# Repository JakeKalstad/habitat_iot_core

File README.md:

# Habitat IoT

**Rust firmware and hardware designs for connected sensors and actuators, built around the ESP32.**

Habitat began in 2023 as the device side of a larger IoT platform. It brings together embedded firmware, browser-based Wi-Fi setup, local device management, sensor telemetry, and hardware designs in one project.

The original implementation predates our use of LLM-assisted development. We are releasing it so others can study the design, reuse the device interfaces, and build on the work.

**This release covers the device side. The platform it originally integrated with remains proprietary and is not included.** You can build an independent integration using the HTTP endpoints, MQTT messages, and shared Rust types described below. Access to the original platform is not supplied with this repository.

## What is here

- ESP32 firmware written in Rust, using ESP-IDF through `esp-idf-svc` and `esp-idf-hal`.
- Browser-based Wi-Fi provisioning and a local administration page.
- Persistent Wi-Fi, device, and MQTT settings in ESP32 non-volatile storage (NVS).
- Local HTTP endpoints for health information, sensor readings, and configuration.
- Optional MQTT publishing and mDNS service discovery.
- Compile-time modules for environmental sensors, digital inputs, a display, and actuators.
- Shared message types, a simulated device publisher, KiCad designs, and enclosure files.

The firmware uses ESP-IDF and its native components; this is a Rust application on ESP-IDF rather than a `no_std` implementation of the entire device stack.

## Scope and status

This is a historical engineering project being prepared for public use. The supplied snapshot includes later dependency updates and development tooling; it is not a frozen copy of the 2023 toolchain.

The code should be treated as a development starting point. A clean build and physical-device validation are still required for each board and feature combination. Some optional paths are incomplete, hardware configuration needs review, and infrastructure files retain assumptions from the original private environment.

The proprietary hub/backend, platform application, and production services are outside this release. References to them in configuration and deployment files describe the original environment, not services that this repository provides.

## Repository layout

| Path | Purpose |
| --- | --- |
| `iot-core/` | ESP32 firmware, embedded web pages, sensor acquisition, networking, and actuator code. |
| `iot-common/` | Shared serializable types, feature names, and discovery constants. |
| `fake_device/` | Host-side MQTT publisher producing simulated device readings. |
| `schematics/` | KiCad circuit and PCB designs, including environmental sensing boards. |
| `enclosure/` | Enclosure and 3D-print assets, plus reference board files. |
| `pcd8544/` | Local PCD8544 display driver dependency. |
| `kicad-rs/` | KiCad integration library and examples. |
| `devops/` | Historical build, verification, and deployment tooling. Not a standalone platform distribution. |

These are separate Cargo projects, not a single root Cargo workspace. Run commands from the relevant crate directory.

## How a device operates

1. Load the device definition embedded from `iot-core/src/config.json` and any saved user settings from NVS.
2. Scan for Wi-Fi networks. If no SSID is stored, start a setup access point and serve the provisioning page.
3. Save the submitted Wi-Fi settings and restart into client mode.
4. Join the configured network and expose the local administration and data endpoints.
5. Synchronize time with SNTP, perform the hub MQTT discovery query, and enter the acquisition loop.
6. Collect readings from the compiled-in modules and, when enabled, publish them to the configured MQTT broker.

The loop includes a one-second delay, but sensor operations add latency. This is not a guaranteed one-second sampling interval. The current startup path also waits for time synchronization before acquisition begins.

## Build and flash

### Requirements

- An ESP32 board compatible with the configured `xtensa-esp32-espidf` target, a USB data connection, and serial-port access.
- Rust with the Espressif `esp` toolchain, normally installed through `espup`, including `rust-src`.
- `ldproxy` and `espflash` available on your path.
- The native build prerequisites required by ESP-IDF and `embuild` on your host.
- A Wi-Fi network and, if using MQTT, a reachable broker.

The checked-in build configuration selects:

| Setting | Value |
| --- | --- |
| Rust toolchain | `esp` |
| Target | `xtensa-esp32-espidf` |
| MCU | `esp32` |
| ESP-IDF | `v5.2` |
| Runner | `espflash flash --monitor` |

Load the environment exported by your Espressif toolchain installation before building. Preserve the sibling `iot-common/` and `pcd8544/` directories: the firmware manifest references both through local paths.

### Start with a sensorless device

Review `iot-core/src/config.json`, assign a unique device `id`, and check the build notes below. Then, from the repository root:

```sh
cd iot-core
cargo build --release --features bare
cargo run --release --features bare
```

`cargo run` invokes the configured flash-and-monitor runner. These are the intended commands for this configuration, not a claim that this snapshot has been verified against a current toolchain.

Once the bare device works, enable the module you have wired, for example:

```sh
cargo run --release --features bare,temp_humidity
```

Features select firmware code at compile time. Adding an entry to `config.json` does not enable its driver.

## Device configuration

`iot-core/src/config.json` is embedded at build time. It describes device identity, model/version metadata, and feature wiring. Changes require a rebuild and reflash.

A minimal sensorless definition is:

```json
{
  "id": "bench-01",
  "version": "alpha",
  "model": "esp32-wroom",
  "features": {
    "bare": {
      "name": "bare",
      "description": "Sensorless development device",
      "connection_type": "none",
      "hardware_compatible": [],
      "pins": {}
    }
  }
}
```

Use a different ID for each physical device. The supplied `proto-1` value is a development identifier, not an automatically generated serial number.

Wi-Fi credentials, device name/location, and MQTT settings are configured through the device's web interface and saved separately in NVS. They are not part of this build-time JSON.

### Firmware features

| Cargo feature | Implementation / intended role |
| --- | --- |
| `bare` | Sensorless status payload: `{"message":"Here and happy"}`. |
| `temp_humidity` | DHT11 acquisition path; temperature and humidity fields. |
| `temp_pressure` | BMP280 acquisition path; temperature and pressure fields. |
| `motion_sensor` | Digital input reported as a boolean state. |
| `water_sensor` | ADC reading reported as a numeric value. |
| `reed_switch` | Digital input reported as a boolean state. |
| `air_quality` | SGP30 CO₂-equivalent and TVOC readings. |
| `display` | PCD8544 display output using the local driver. |
| `servo` | PWM servo implementation with local HTTP control. |
| `motor` | Experimental L298N motor path; HTTP route registration is commented out. |
| `reset_volatile` | Removes saved Wi-Fi SSID/key at startup; does not clear all device settings. |

Do not enable every feature together by default. Pins, buses, peripheral ownership, and driver compatibility must be checked for the selected combination. The `host` feature is declared but does not establish a host build of the ESP32 firmware.

### Wiring limitations in this snapshot

Treat the configuration as a starting point, not a verified wiring guide:

- The motion configuration names GPIO20, which is absent from the firmware's GPIO map. Its HC-SR04 label also does not match the implemented single-pin boolean acquisition path.
- Several sensor pins in the supplied JSON are absent from the current dynamic GPIO map. Reconcile the map and configuration before enabling those modules.
- The temperature/humidity path calls the DHT11 driver even though the configuration also lists DHT12. Validate the conversion/scaling against actual hardware.
- The pressure path uses a fixed `0x76` address; changing its JSON address alone does not change the driver initialization.
- Display wiring and the servo's GPIO14 configuration are set directly in `main.rs`; not every peripheral is driven by JSON pin assignments.
- The servo performs a startup sweep. Keep attached mechanisms clear during development.

## Provision and configure

1. Flash and power the device.
2. If no Wi-Fi SSID is saved, look for its `HABITAT-` prefixed setup network. The current formatter adds another hyphen after that prefix.
3. Connect and open the device's access-point gateway address in a browser. The code does not provide a captive-portal DNS redirect.
4. Choose the target network, submit its credentials, and allow the device to restart.
5. Find the device's LAN address through your router or mDNS and open `http://DEVICE_IP/`.
6. Set its name, location, MQTT broker URL, optional broker credentials, and MQTT enable checkbox as required.

The admin forms persist changes and restart the device. For a typical local broker, the URL takes the form `mqtt://BROKER_IP:1883`.

To provision again, use the admin page's network-clear action. If the device is unreachable, the `reset_volatile` build feature removes the stored SSID/key on boot. Remove that feature from subsequent builds so credentials persist normally.

## Integrate with your own backend

Your service can poll HTTP or subscribe to MQTT without implementing the proprietary platform. `iot-common/src/lib.rs` defines the shared payload structures.

### Local HTTP interface

| Method | Path | Purpose |
| --- | --- | --- |
| `GET` | `/` | Provisioning page in setup mode; administration page when connected. |
| `POST` | `/upload` | Setup-mode Wi-Fi submission. |
| `GET` | `/heartbeat` | Connected-mode version, model, timestamp, and MQTT-enabled state. |
| `GET` | `/data` | Latest readings and their acquisition timestamp. |
| `POST` | `/set_network` | Save Wi-Fi settings and restart. |
| `POST` | `/set_device_data` | Save device name/location and restart. |
| `POST` | `/set_mqtt` | Save MQTT configuration and restart. |
| `POST` | `/clear_network` | Clear Wi-Fi SSID/key and restart. |
| `GET` | `/servo/coordinate` | Read the angle calculated from PWM duty, when `servo` is compiled in. |
| `POST` | `/servo/coordinate` | Set a servo destination using JSON, e.g. `{"destination":90.0}`. |

Configuration routes accept HTML form submissions. The servo readback is a calculated commanded angle, not physical position feedback.

```sh
curl http://DEVICE_IP/heartbeat
curl http://DEVICE_IP/data
```

Illustrative `/data` response:

```json
{
  "data": {
    "bare": "{\"message\":\"Here and happy\"}"
  },
  "timestamp": 1700000000000
}
```

The outer response is JSON, but each value inside `data` is itself a JSON-encoded **string**. Parse the response, then parse each feature value. Timestamps in `/data` and `/heartbeat` are Unix epoch milliseconds; MQTT feature messages do not include that wrapper timestamp.

### MQTT telemetry

The firmware publishes one message per available feature using this topic structure:

```text
device/{id}/{model}/{device_name}/{device_location}/{feature}/data
```

For example:

```text
device/bench-01/esp32-wroom/bench/lab/bare/data
```

Payload:

```json
{"message":"Here and happy"}
```

Firmware messages use QoS 0 and are not retained. If no user name is configured, the firmware derives one from model, features, and ID; the default location is `home`. Keep topic components free of `/`, `+`, and `#` when assigning names and locations.

The broker URL is taken from saved settings. Although the firmware queries the original hub's MQTT mDNS service, it does not use that query result to populate the broker configuration.

**Multi-device caveat:** the firmware currently uses the fixed MQTT client ID `test_publish`. Assign a unique client ID per device before connecting multiple boards to the same broker.

### Discovery

Devices advertise `_habitat_iot._tcp` on port 80. TXT metadata includes build time, model, enabled products/features, device name, and location. The hostname is derived as `habitat_iot-{id}`.

The firmware also queries the service instance `habitat_iot_hub_mqtt` under `_mqtt._tcp`. These names are historical integration conventions, not an included backend implementation. Use the device's IP if your network or resolver does not handle the advertised hostname.

### Payload fields

| Feature | JSON fields |
| --- | --- |
| `bare` | `message` |
| `temp_humidity` | `temperature`, `humidity` |
| `temp_pressure` | `temperature`, `pressure` |
| `motion_sensor`, `reed_switch` | `state` |
| `water_sensor` | `value` |
| `air_quality` | `co2_ppm`, `tvoc_ppb` |

The SGP30 `co2_ppm` field contains the driver's CO₂-equivalent estimate. The water sensor value is an ADC reading, not a calibrated water-level measurement. Confirm units and calibration before using readings for automation.

## Simulated devices

`fake_device/` publishes synthetic readings to an MQTT broker and advertises mDNS metadata, allowing backend integration work without a physical board. It does not implement the firmware's HTTP server.

Its manifest still references the original private Git source for `iot-common`. For an independent checkout, replace that dependency with:

```toml
iot-common = { path = "../iot-common" }
```

Then, from `fake_device/`:

```sh
MOSQUITTO_HOST=127.0.0.1 \
MOSQUITTO_PORT=1883 \
DEVICE_COUNT=1 \
cargo run
```

`MOSQUITTO_USER` and `MOSQUITTO_PASSWORD` are optional environment variables. A local `.env` file is also supported; keep credentials out of version control.

The simulator publishes approximately every 2.5 seconds and retains its messages, unlike the firmware. Its current `1..device_count` loop creates `DEVICE_COUNT - 1` devices when the requested count exceeds one. Account for or correct that behavior when testing fleets.

## Hardware designs

`schematics/` contains KiCad source files and board assets. `enclosure/` contains mechanical and printing assets. These are useful alongside the firmware when adapting the project to a physical device.

Review each design's parts, pin assignments, electrical requirements, and licence before fabrication. Bundled reference hardware and libraries may carry separate terms; the repository is not a single, uniformly licensed hardware design.

## Development notes

- Begin with `bare`, establish provisioning and local HTTP access, then add one hardware module at a time.
- Review dependency versions before updating them. Several manifests use wildcard versions, so resolution is not fully reproducible.
- Treat `devops/` scripts and Kubernetes manifests as historical references. They assume private services, repositories, images, and infrastructure.
- Some tooling paths need repair. For example, `devops/verify_kicad` points to `../kicad-rs`, while the bundled library is at the repository root.
- Keep changes focused and include the board model, enabled features, wiring, and relevant serial logs when reporting firmware issues. Redact credentials from logs.

Useful contributions include reproducible builds, corrected board configurations, driver updates, sensor calibration, clearer hardware documentation, and independent integrations.

## Security

This snapshot has no application authentication on its HTTP administration or actuator routes. The administration page renders stored credentials into its HTML, and configuration handlers print some submitted credentials to serial logs. Provisioning also contains a hard-coded development AP password value; do not rely on it as an access-control boundary.

Run it on an isolated, trusted development network. Add authentication, appropriate transport protection, input validation, credential handling, and actuator safeguards before deploying beyond that environment. The firmware has no demonstrated production security hardening in this release.

## Licensing

A project-wide licence has not yet been supplied in this snapshot. The planned public release needs an explicit licence for the original firmware and a stated licence for the original hardware designs before reuse permissions are clear.

Third-party components retain their own notices and terms, including the licences bundled with `pcd8544/`, `kicad-rs/`, and the reference hardware under `enclosure/`. Those licences do not automatically apply to the rest of Habitat. The proprietary platform is outside the scope of this release.

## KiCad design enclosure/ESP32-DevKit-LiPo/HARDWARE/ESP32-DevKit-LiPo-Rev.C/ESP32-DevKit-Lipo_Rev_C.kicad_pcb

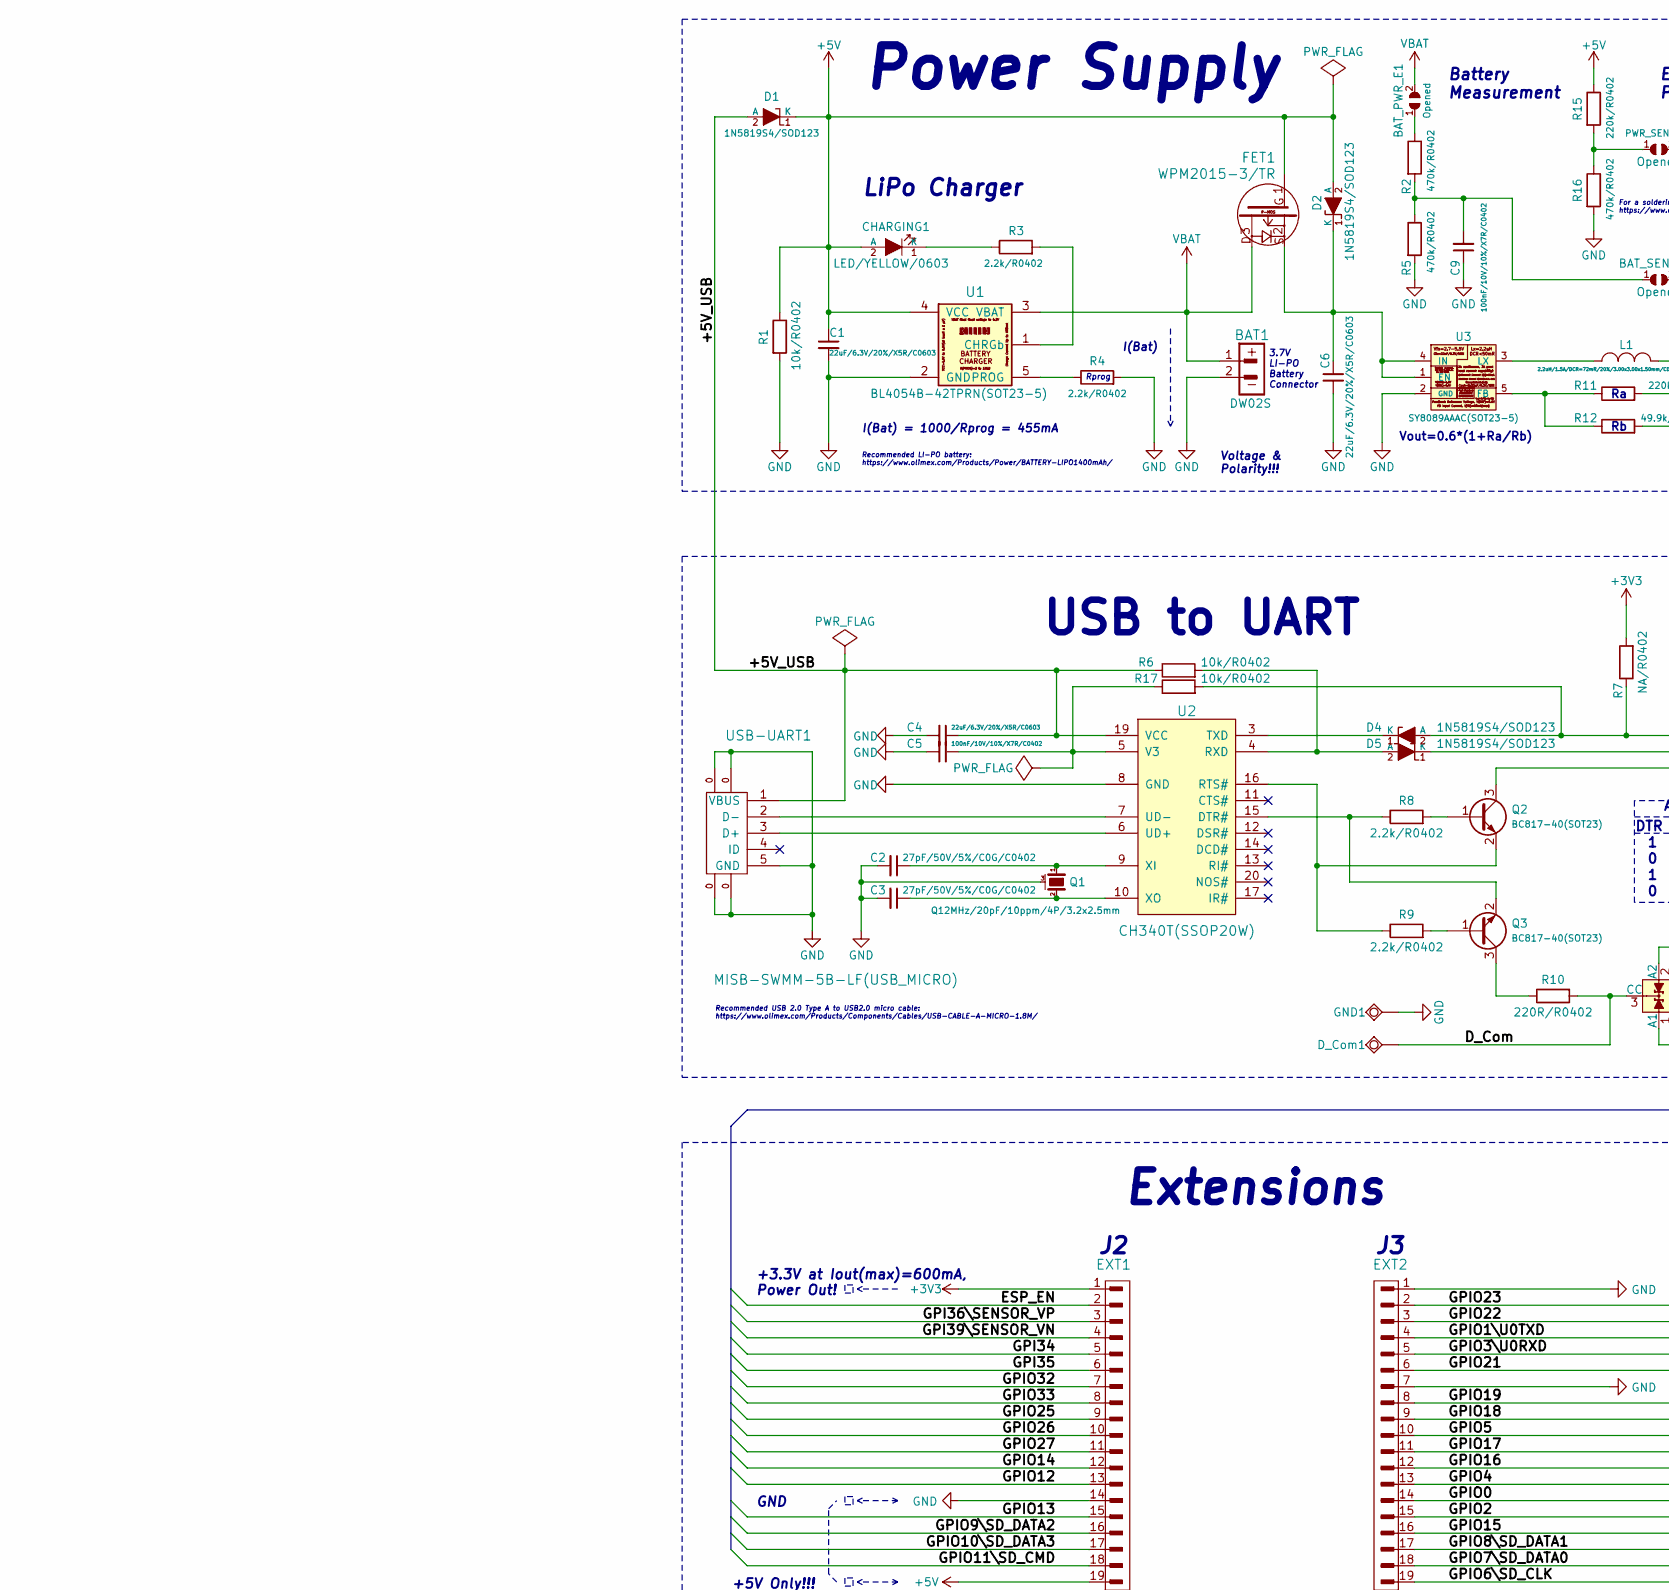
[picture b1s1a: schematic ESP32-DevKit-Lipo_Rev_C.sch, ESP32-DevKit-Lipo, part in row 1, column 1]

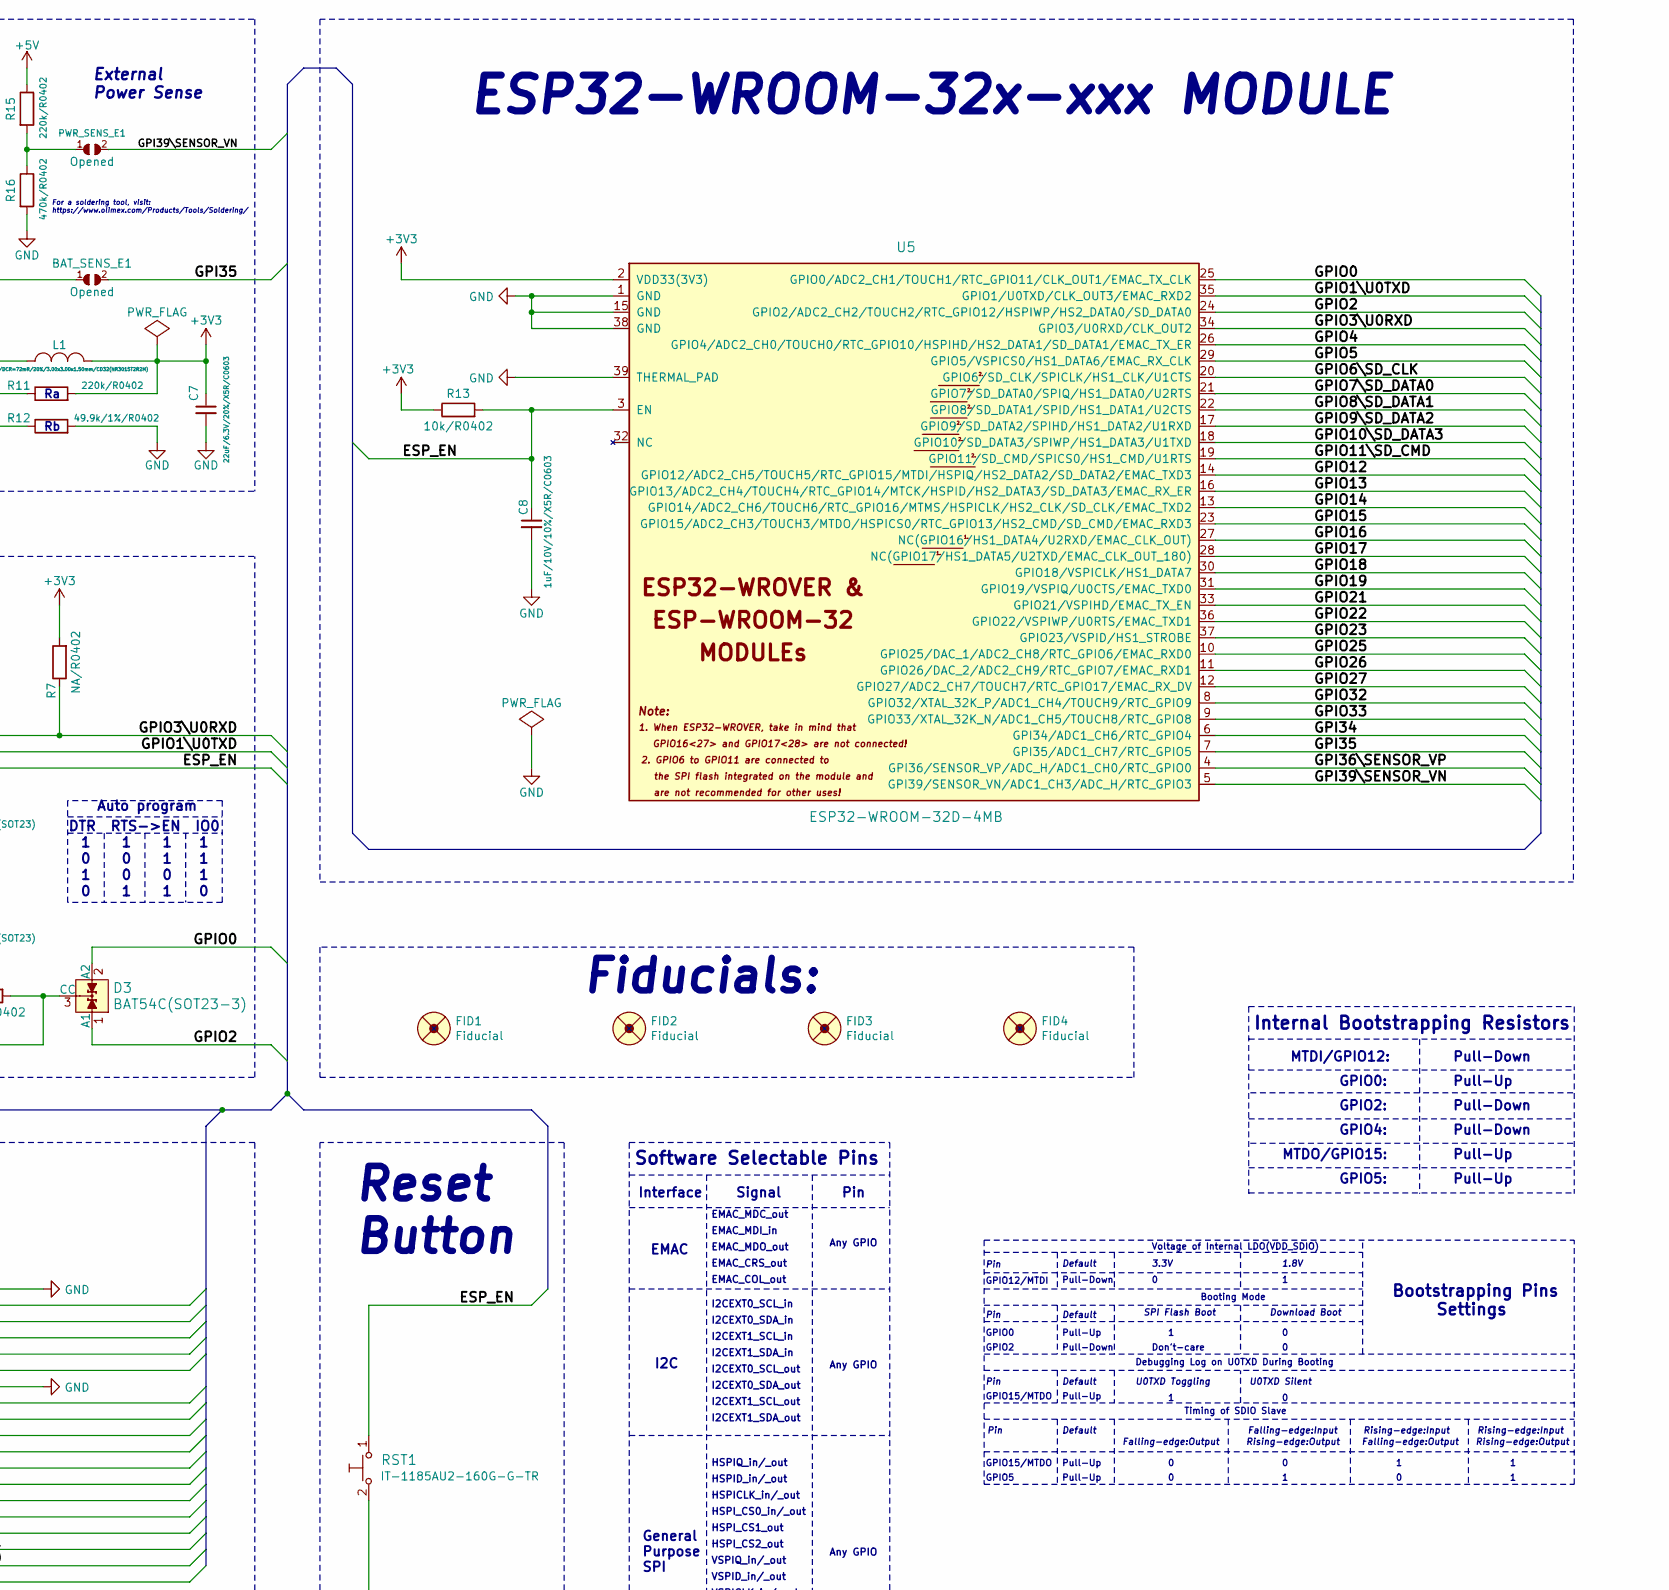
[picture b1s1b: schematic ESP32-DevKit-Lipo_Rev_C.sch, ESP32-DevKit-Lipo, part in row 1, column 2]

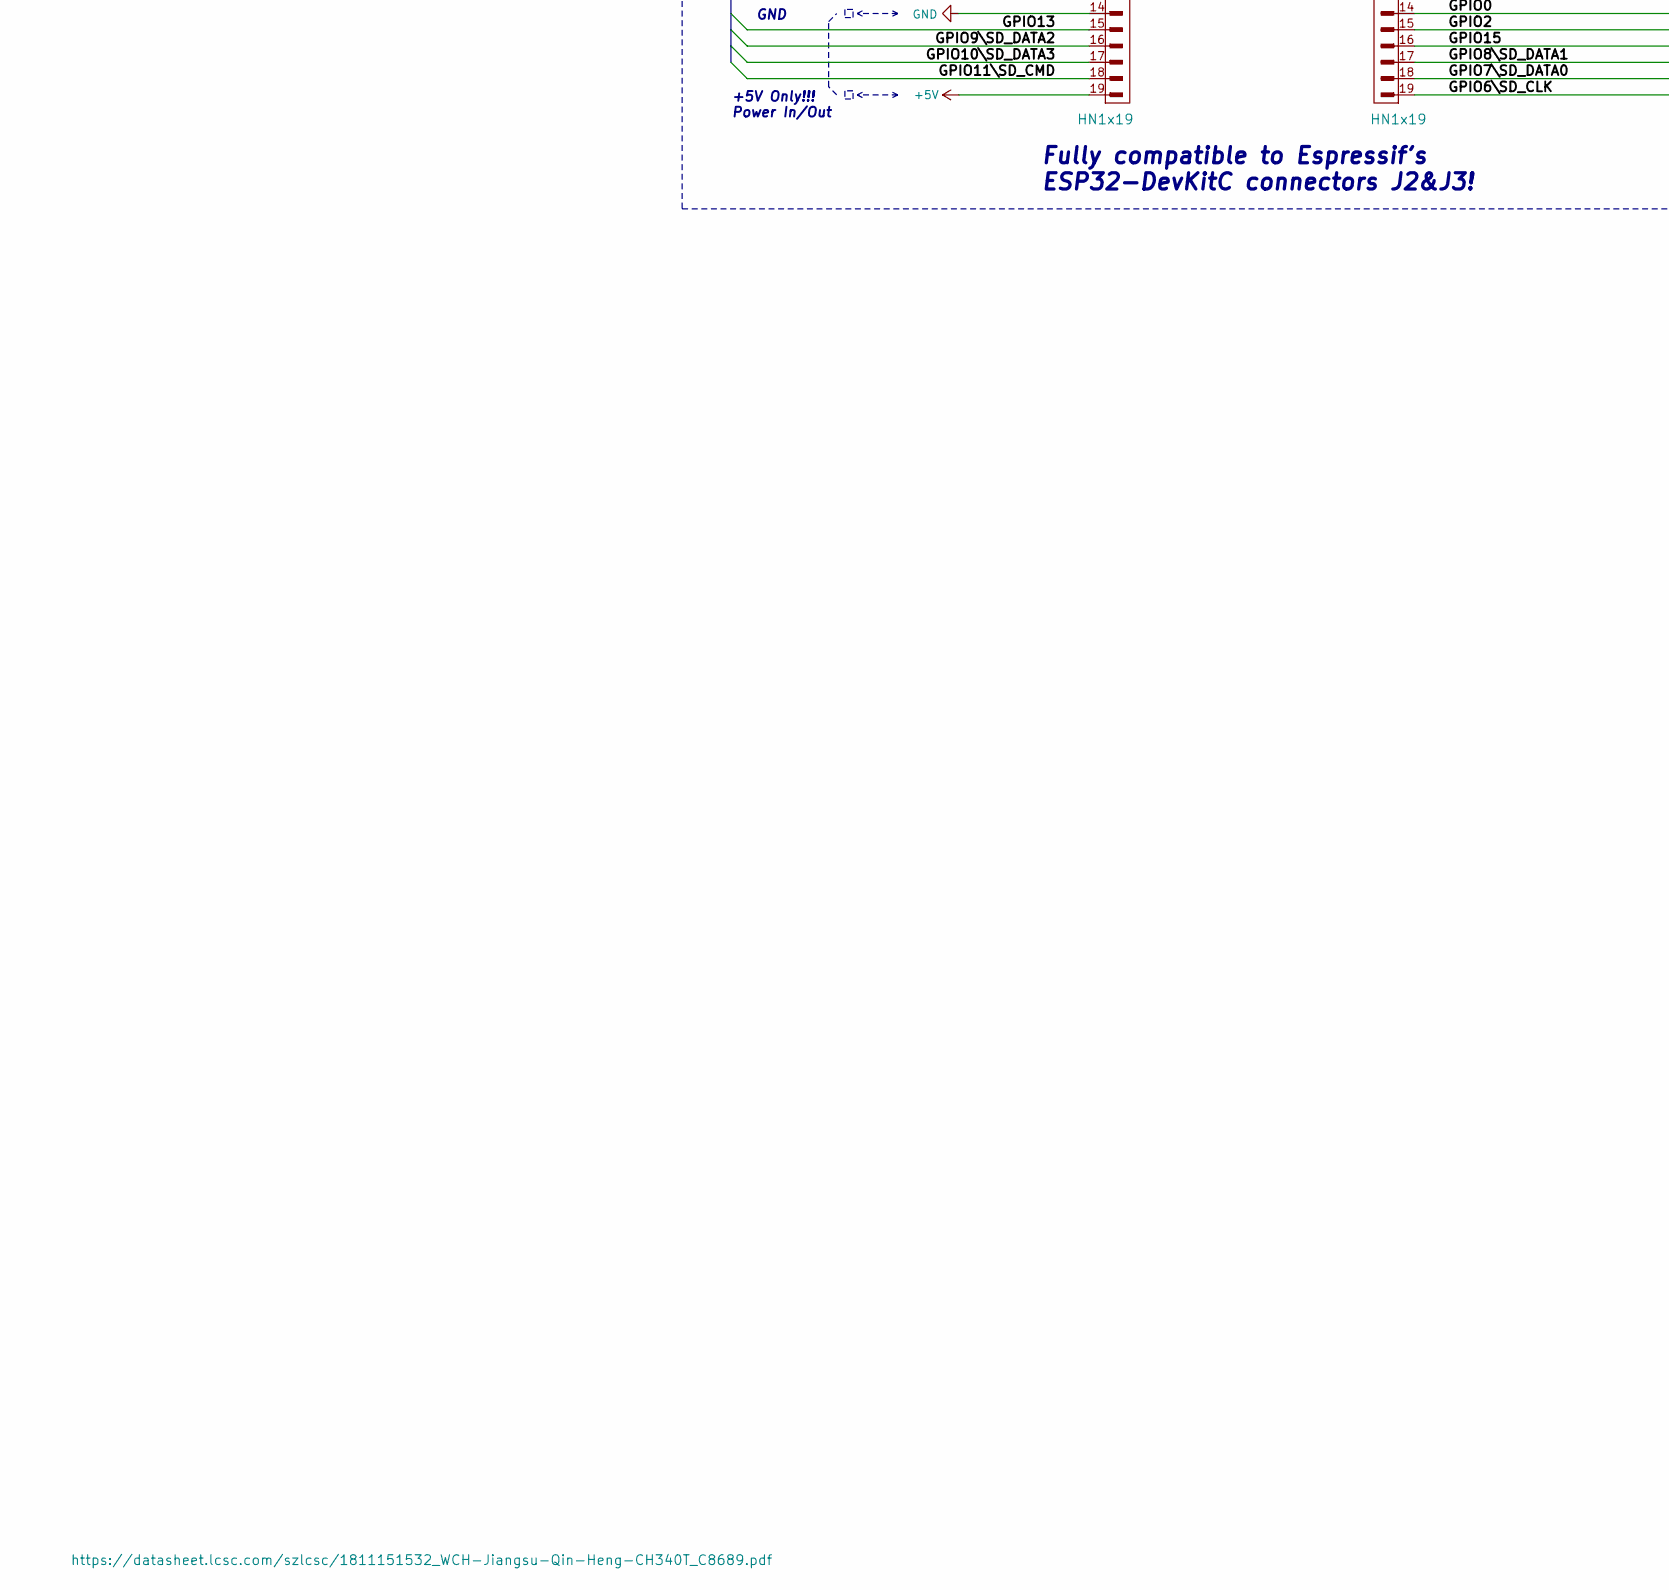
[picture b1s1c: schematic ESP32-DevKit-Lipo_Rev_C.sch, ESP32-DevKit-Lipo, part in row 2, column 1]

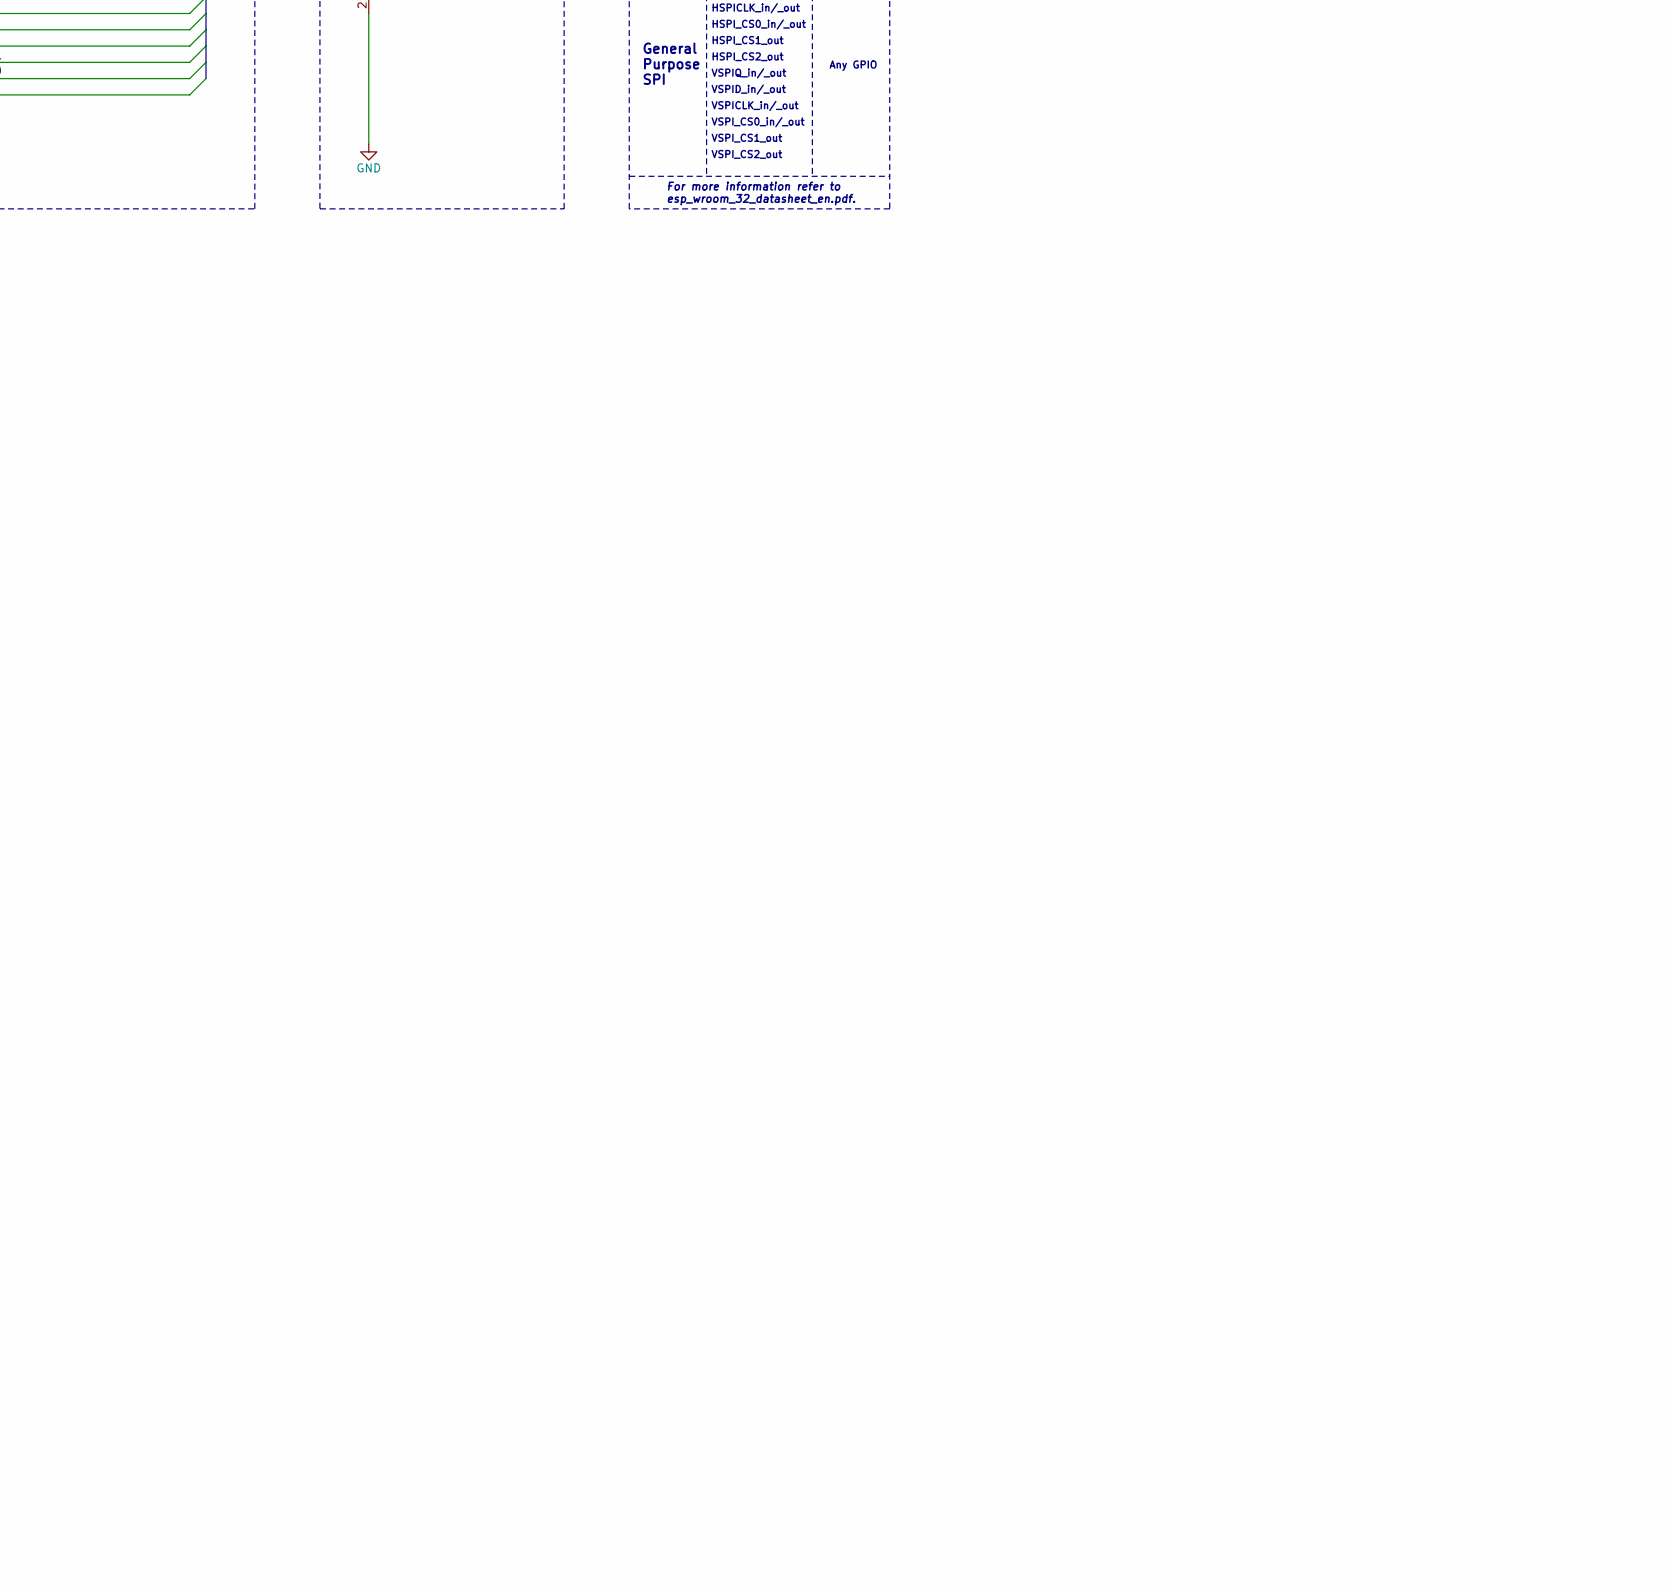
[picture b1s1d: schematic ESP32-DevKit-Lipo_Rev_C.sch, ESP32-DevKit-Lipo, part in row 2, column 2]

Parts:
BAT1: DW02S; LIPO_BAT_VERTICAL_DW02S
BAT_PWR_E1: Opened; SJ_1_SMALLER
BAT_SENS_E1: Opened; SJ_1_SMALLER
C1, C4, C6, C7: 22uF/6.3V/20%/X5R/C0603; C_0603_5MIL_DWS
C2, C3: 27pF/50V/5%/C0G/C0402; C_0402_5MIL_DWS
C5, C9: 100nF/10V/10%/X7R/C0402; C_0402_5MIL_DWS
C8: 1uF/10V/10%/X5R/C0603; C_0603_5MIL_DWS
CHARGING1: LED/YELLOW/0603; LED_0603_KA
D1, D2, D4, D5: 1N5819S4/SOD123; SOD-123_1C-2A_KA
D3: BAT54C(SOT23-3); SOT23-3
D_Com1: TESTPAD; TESTPAD_40-ROUND
EXT1, EXT2: HN1x19
FET1: WPM2015-3/TR; SOT23
FID1, FID2, FID3, FID4: Fiducial; Fiducial1x3
GND1: TESTPAD; TESTPAD_40-ROUND
L1: 2.2uH/1.5A/DCR=72mR/20%/3.00x3.00x1.50mm/CD32(NR3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; CD32
PWR_SENS_E1: Opened; SJ_1_SMALLER
Q1: Q12MHz/20pF/10ppm/4P/3.2x2.5mm; TSX-3.2x2.5mm_GND(3)
Q2, Q3: BC817-40(SOT23); SOT23
R1, R6, R13, R17: 10k/R0402; R_0402_5MIL_DWS
R2, R5, R16: 470k/R0402; R_0402_5MIL_DWS
R3, R4, R8, R9: 2.2k/R0402; R_0402_5MIL_DWS
R7: NA/R0402; R_0402_5MIL_DWS
R10: 220R/R0402; R_0402_5MIL_DWS
R11, R15: 220k/R0402; R_0402_5MIL_DWS
R12: 49.9k/1%/R0402; R_0402_5MIL_DWS
RST1: IT-1185AU2-160G-G-TR; IT1185AU2_V2
U1: BL4054B-42TPRN(SOT23-5); SOT-23-5
U2: CH340T(SSOP20W); SSOP-20W
U3: SY8089AAAC(SOT23-5); SOT-23-5
U5: ESP32-WROOM-32D-4MB; ESP32-WROVER_MODULE
USB-UART1: MISB-SWMM-5B-LF(USB_MICRO); USB-MICRO_MISB-SWMM-5B_LF

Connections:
+3V3: C7.1, EXT1.1, L1.2, R7.2, R11.2, R13.1, U5.2 (VDD33(3V3))
+5V: C1.1, CHARGING1.2 (A), D1.1 (K), D2.2 (A), EXT1.19, FET1.1, R1.1, R15.1, U1.4 (VCC)
/+5V_USB: C4.1, D1.2 (A), R6.1, U2.19 (VCC), USB-UART1.1 (VBUS)
/D_Com: D3.3 (CC), D_Com1.1 (Pad), R10.2
/ESP_EN: C8.1, EXT1.2, Q2.3 (C), R13.2, RST1.1, U5.3 (EN)
/GPI34: EXT1.5, U5.6 (GPI34/ADC1_CH6/RTC_GPIO4)
/GPI35: BAT_SENS_E1.2, EXT1.6, U5.7 (GPI35/ADC1_CH7/RTC_GPIO5)
/GPI36\SENSOR_VP: EXT1.3, U5.4 (GPI36/SENSOR_VP/ADC_H/ADC1_CH0/RTC_GPIO0)
/GPI39\SENSOR_VN: EXT1.4, PWR_SENS_E1.2, U5.5 (GPI39/SENSOR_VN/ADC1_CH3/ADC_H/RTC_GPIO3)
/GPIO0: D3.2 (A2), EXT2.14, U5.25 (GPIO0/ADC2_CH1/TOUCH1/RTC_GPIO11/CLK_OU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)
/GPIO1\U0TXD: D5.1 (K), EXT2.4, U5.35 (GPIO1/U0TXD/CLK_OUT3/EMAC_RXD2)
/GPIO2: D3.1 (A1), EXT2.15, U5.24 (GPIO2/ADC2_CH2/TOUCH2/RTC_GPIO12/HSPIWP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)
/GPIO3\U0RXD: D4.2 (A), EXT2.5, R7.1, R17.2, U5.34 (GPIO3/U0RXD/CLK_OUT2)
/GPIO4: EXT2.13, U5.26 (GPIO4/ADC2_CH0/TOUCH0/RTC_GPIO10/HSPIHD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)
/GPIO5: EXT2.10, U5.29 (GPIO5/VSPICS0/HS1_DATA6/EMAC_RX_CLK)
/GPIO6\SD_CLK: EXT2.19, U5.20 (GPIO6/SD_CLK/SPICLK/HS1_CLK/U1CTS)
/GPIO7\SD_DATA0: EXT2.18, U5.21 (GPIO7/SD_DATA0/SPIQ/HS1_DATA0/U2RTS)
/GPIO8\SD_DATA1: EXT2.17, U5.22 (GPIO8/SD_DATA1/SPID/HS1_DATA1/U2CTS)
/GPIO9\SD_DATA2: EXT1.16, U5.17 (GPIO9/SD_DATA2/SPIHD/HS1_DATA2/U1RXD)
/GPIO10\SD_DATA3: EXT1.17, U5.18 (GPIO10/SD_DATA3/SPIWP/HS1_DATA3/U1TXD)
/GPIO11\SD_CMD: EXT1.18, U5.19 (GPIO11/SD_CMD/SPICS0/HS1_CMD/U1RTS)
/GPIO12: EXT1.13, U5.14 (GPIO12/ADC2_CH5/TOUCH5/RTC_GPIO15/MTDI/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)
/GPIO13: EXT1.15, U5.16 (GPIO13/ADC2_CH4/TOUCH4/RTC_GPIO14/MTCK/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)
/GPIO14: EXT1.12, U5.13 (GPIO14/ADC2_CH6/TOUCH6/RTC_GPIO16/MTMS/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)
/GPIO15: EXT2.16, U5.23 (GPIO15/ADC2_CH3/TOUCH3/MTDO/HSPICS0/RTC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)
/GPIO16: EXT2.12, U5.27 (NC(GPIO16/HS1_DATA4/U2RXD/EMAC_CLK_OUT))
/GPIO17: EXT2.11, U5.28 (NC(GPIO17/HS1_DATA5/U2TXD/EMAC_CLK_OUT_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)
/GPIO18: EXT2.9, U5.30 (GPIO18/VSPICLK/HS1_DATA7)
/GPIO19: EXT2.8, U5.31 (GPIO19/VSPIQ/U0CTS/EMAC_TXD0)
/GPIO21: EXT2.6, U5.33 (GPIO21/VSPIHD/EMAC_TX_EN)
/GPIO22: EXT2.3, U5.36 (GPIO22/VSPIWP/U0RTS/EMAC_TXD1)
/GPIO23: EXT2.2, U5.37 (GPIO23/VSPID/HS1_STROBE)
/GPIO25: EXT1.9, U5.10 (GPIO25/DAC_1/ADC2_CH8/RTC_GPIO6/EMAC_RX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)
/GPIO26: EXT1.10, U5.11 (GPIO26/DAC_2/ADC2_CH9/RTC_GPIO7/EMAC_RX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)
/GPIO27: EXT1.11, U5.12 (GPIO27/ADC2_CH7/TOUCH7/RTC_GPIO17/EMAC_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)
/GPIO32: EXT1.7, U5.8 (GPIO32/XTAL_32K_P/ADC1_CH4/TOUCH9/RTC_G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)
/GPIO33: EXT1.8, U5.9 (GPIO33/XTAL_32K_N/ADC1_CH5/TOUCH8/RTC_G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)
GND: BAT1.2, C1.2, C2.2, C3.2, C4.2, C5.2, C6.2, C7.2, C8.2, C9.1, EXT1.14, EXT2.1, EXT2.7, GND1.1 (Pad), Q1.3 (case), R1.2, R4.2, R5.2, R12.2, R16.2, RST1.2, U1.2 (GND), U2.8 (GND), U3.2 (GND), U5.1 (GND), U5.15 (GND), U5.38 (GND), U5.39 (THERMAL_PAD), USB-UART1.0, USB-UART1.5 (GND)
unnamed: BAT_PWR_E1.1, R2.1
unnamed: BAT_SENS_E1.1, C9.2, R2.2, R5.1
unnamed: CHARGING1.1 (K), R3.1
unnamed: C6.1, D2.1 (K), FET1.2, U3.1 (EN), U3.4 (IN)
unnamed: D4.1 (K), U2.3 (TXD)
unnamed: D5.2 (A), R6.2, U2.4 (RXD)
unnamed: PWR_SENS_E1.1, R15.2, R16.1
unnamed: Q2.1 (B), R8.2
unnamed: Q2.2 (E), R9.1, U2.16 (RTS#)
unnamed: Q3.1 (B), R9.2
unnamed: Q3.3 (C), R10.1
unnamed: Q3.2 (E), R8.1, U2.15 (DTR#)
unnamed: R3.2, U1.1 (CHRGb)
unnamed: R4.1, U1.5 (PROG)
unnamed: U2.6 (UD+), USB-UART1.3 (D+)
unnamed: U2.7 (UD-), USB-UART1.2 (D-)
unnamed: C5.1, R17.1, U2.5 (V3)
unnamed: C2.1, Q1.1, U2.9 (XI)
unnamed: C3.1, Q1.2, U2.10 (XO)
unnamed: R11.1, R12.1, U3.5 (FB)
unnamed: L1.1, U3.3 (LX)
VBAT: BAT1.1, BAT_PWR_E1.2, FET1.3, U1.3 (VBAT)

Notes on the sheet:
GPIO2:
Default
SPI Flash Boot
Any GPIO
Pull-Down
Signal
HSPIQ_in/_out
EMAC_MDC_out
Bootstrapping Pins Settings
GPIO12/MTDI
GPIO0:
I(Bat)
ESP32-WROOM-32x-xxx MODULE
I2CEXT1_SCL_out
Battery Measurement
I2CEXT1_SCL_in
HSPID_in/_out
Debugging Log on U0TXD During Booting
Pin
I2CEXT0_SCL_out
Vout=0.6*(1+Ra/Rb)
Auto program
General Purpose SPI
VSPIQ_in/_out
Pull-Up
I2CEXT0_SCL_in
I(Bat) = 1000/Rprog = 455mA
Falling-edge:Input
Don't-care
VSPI_CS0_in/_out
GPIO0
GPIO4:
Rising-edge:Output
HSPI_CS0_in/_out
VSPID_in/_out
EMAC_COL_out
GPIO15/MTDO
I2CEXT0_SDA_in
EMAC_CRS_out
LiPo Charger

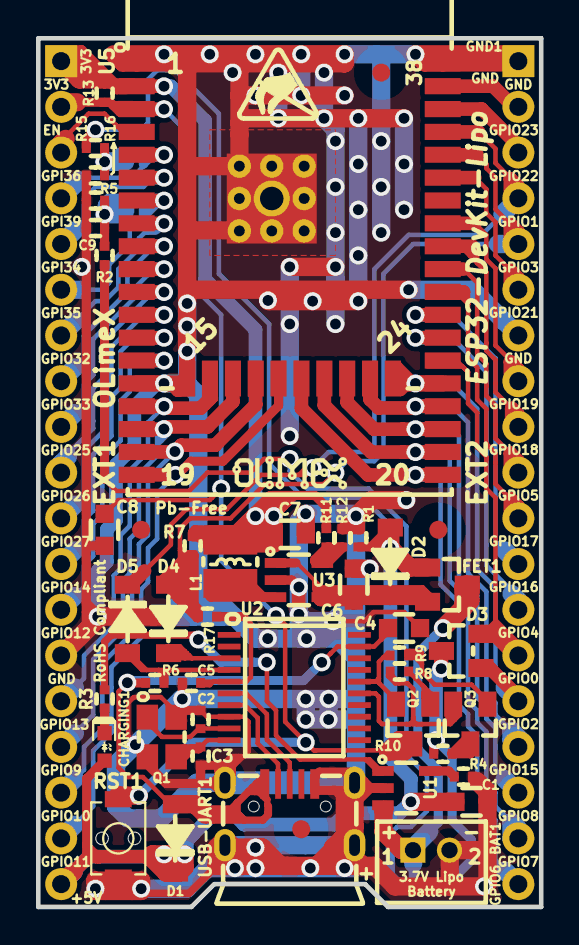
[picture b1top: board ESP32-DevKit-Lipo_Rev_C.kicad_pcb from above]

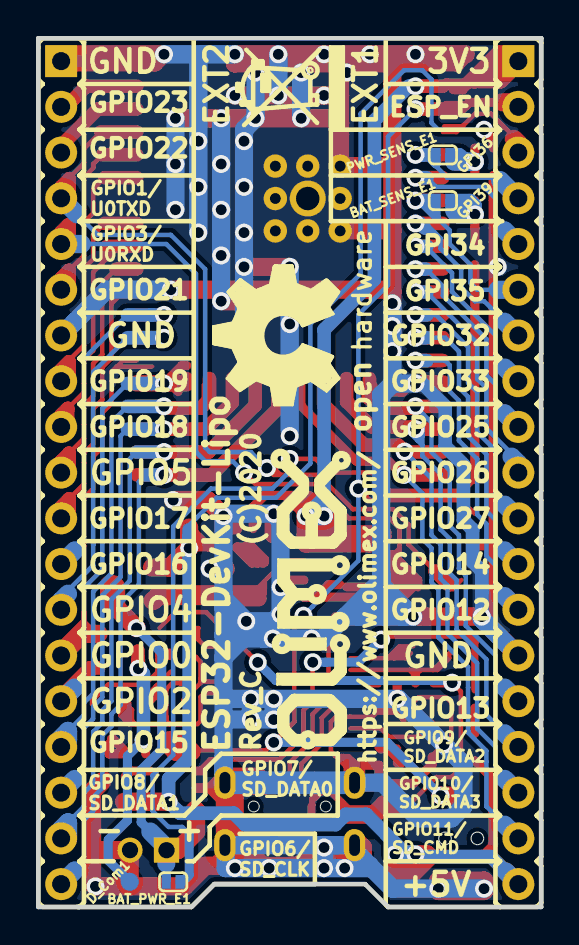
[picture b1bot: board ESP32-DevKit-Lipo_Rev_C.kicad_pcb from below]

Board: 2 copper layers, 27.9 x 48.3 mm, 59 parts (9 on the bottom side), 60 nets.

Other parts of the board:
Logo_OSHW: LOGO_OPENHARDWARE_8x8
Olimex_Logo_Big: OLIMEX_LOGO_TB
Olimex_Logo_Small: LOGO_OLIMEX_80
Sign_Antistatic: Val**; LOGO_ANTISTATIC_SMALL_4.5mmX2.8mm
Sign_RecycleBin: LOGO_RECYCLEBIN_1

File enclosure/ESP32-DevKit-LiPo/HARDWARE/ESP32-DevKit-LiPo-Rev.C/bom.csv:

"Reference","Value","Datasheet","Footprint","Qty","DNP"
"BAT1","DW02S","","OLIMEX_Connectors-FP:LIPO_BAT_VERTICAL_DW02S","1",""
"BAT_PWR_E1,BAT_SENS_E1,PWR_SENS_E1","Opened","","OLIMEX_Jumpers-FP:SJ_1_SMALLER","3",""
"C1,C4,C6,C7","22uF/6.3V/20%/X5R/C0603","","OLIMEX_RLC-FP:C_0603_5MIL_DWS","4",""
"C2,C3","27pF/50V/5%/C0G/C0402","","OLIMEX_RLC-FP:C_0402_5MIL_DWS","2",""
"C5,C9","100nF/10V/10%/X7R/C0402","","OLIMEX_RLC-FP:C_0402_5MIL_DWS","2",""
"C8","1uF/10V/10%/X5R/C0603","","OLIMEX_RLC-FP:C_0603_5MIL_DWS","1",""
"CHARGING1","LED/YELLOW/0603","","OLIMEX_LEDs-FP:LED_0603_KA","1",""
"D1,D2,D4,D5","1N5819S4/SOD123","","OLIMEX_Diodes-FP:SOD-123_1C-2A_KA","4",""
"D3","BAT54C(SOT23-3)","","OLIMEX_Diodes-FP:SOT23-3","1",""
"D_Com1,GND1","TESTPAD","","OLIMEX_Other-FP:TESTPAD_40-ROUND","2",""
"EXT1,EXT2","HN1x19","","OLIMEX_Connectors-FP:HN1x19","2",""
"FET1","WPM2015-3/TR","","OLIMEX_Transistors-FP:SOT23","1",""
"FID1,FID2,FID3,FID4","Fiducial","","OLIMEX_Other-FP:Fiducial1x3","4",""
"L1","2.2uH/1.5A/DCR=72mR/20%/3.00x3.00x1.50mm/CD32(NR3015T2R2M)","","OLIMEX_RLC-FP:CD32","1",""
"Q1","Q12MHz/20pF/10ppm/4P/3.2x2.5mm","","OLIMEX_Crystal-FP:TSX-3.2x2.5mm_GND(3)","1",""
"Q2,Q3","BC817-40(SOT23)","","OLIMEX_Transistors-FP:SOT23","2",""
"R1,R6,R13,R17","10k/R0402","","OLIMEX_RLC-FP:R_0402_5MIL_DWS","4",""
"R2,R5,R16","470k/R0402","","OLIMEX_RLC-FP:R_0402_5MIL_DWS","3",""
"R3,R4,R8,R9","2.2k/R0402","","OLIMEX_RLC-FP:R_0402_5MIL_DWS","4",""
"R7","NA/R0402","","OLIMEX_RLC-FP:R_0402_5MIL_DWS","1",""
"R10","220R/R0402","","OLIMEX_RLC-FP:R_0402_5MIL_DWS","1",""
"R11,R15","220k/R0402","","OLIMEX_RLC-FP:R_0402_5MIL_DWS","2",""
"R12","49.9k/1%/R0402","","OLIMEX_RLC-FP:R_0402_5MIL_DWS","1",""
"RST1","IT-1185AU2-160G-G-TR","","OLIMEX_Buttons-FP:IT1185AU2_V2","1",""
"U1","BL4054B-42TPRN(SOT23-5)","https://datasheet.lcsc.com/szlcsc/BL4054B-42TPRN_C83783.pdf","OLIMEX_IC-FP:SOT-23-5","1",""
"U2","CH340T(SSOP20W)","https://datasheet.lcsc.com/szlcsc/1811151532_WCH-Jiangsu-Qin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","OLIMEX_IC-FP:SSOP-20W","1",""
"U3","SY8089AAAC(SOT23-5)","https://datasheet.lcsc.com/szlcsc/1810311621_BL-Shanghai-Bel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","OLIMEX_Regulators-FP:SOT-23-5","1",""
"U5","ESP32-WROOM-32D-4MB","https://www.espressif.com/sites/default/files/documentation/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","OLIMEX_Cases-FP:ESP32-WROVER_MODULE","1",""
"USB-UART1","MISB-SWMM-5B-LF(USB_MICRO)","","OLIMEX_Connectors-FP:USB-MICRO_MISB-SWMM-5B_LF","1",""

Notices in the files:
enclosure/ESP32-DevKit-LiPo/HARDWARE/ESP32-DevKit-LiPo-Rev.C/ESP32-DevKit-Lipo_Rev_C.kicad_pcb:
Rev_C (C)2020
